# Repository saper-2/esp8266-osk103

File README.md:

# Rotenso ESP8266-OSK103

This is basically a my version of Sergey's [IoT-Uni-Dongle](https://github.com/dudanov/iot-uni-dongle) . I have created this for my Rotenso branded A/C (and any other A/C that take OSK103 or newer OSK105 wifi module). 

---
**Why**
Someone who see this first time will think **Why**. First, for me it is: **I DO NOT TRUST CHINESE CLOUD**, why I would potentially let someone into my network? Even if those modules don't have this kind of "feature" (supposedly :upside_down_face:). 

E.g.: for hackers that got into manufacturer servers would be then simple to remotely upload firmware that would create encrypted tunnel from their server to inside my home network. Well, someone can say this won't happen, but I in last year, I read about chinese server hacked and that company stayed quiet about it, until stolen data made into black market and started popping up everywhere...

And, there is another much simpler reason: when my internet connection fail then those "cloud-based" solution go to hike... You can't control them via phone being in home (and looking for remote in this case can be PITA :sweat_smile: ), but with custom module that connect to your local server (HomeAssistant, or MQTT, ...) you still in control :grin: 

---

There is not much to write about the module circuit it basically that same. I have made PCB so it can be used with USB male SMT plug, or pinheader/goldpin or JST 2.5mm 4pin (or 5pin if IR is used) or wires just soldered to it. I placed a small 6pin 1mm connector for potential programming, and also testpoint pads that are used by designed especially for this module Programming Rig (cradle).

It's 2nd revision - don't ask about 1st one :upside_down_face:

---

# Part List

## Module

See notes under the list too.

REF | QTY | VAL | Footprint | P/N
--- | --- | --- | --- | ---
C1 C4 | 2 | 100n | C_0402_HS | |
C2 C3 | 2| 22/10V| CP_3216-HS
C5 | 1| 1u| C_0402_HS
C6 | 1| 470p| C_0805_HS
C7 | 1| 15/6,3V| CP_3216-HS
D1 | 1| G| LED0603_HS
D2 | 1| Or| LED0603_HS
D3 | 1| Y| LED0603_HS
FB1 | 1| Z600| R_0805_HS|
J1 | 1| *notes*| 
J2 | 1| *notes*| 
J3*| 1| *notes*| 
M1 | 1| ESP-12E| ESP-12E
R1 R8 R9 | 3| 4k3| R_0402_HS
R10 R12 | 2| 10k| R_0402_HS
R13* R14* | 2| 10k| R_0402_HS2
R15* | 1| 470R| R_0603_HS
R2 R3 | 2| 22R| R_0402_HS
R4 R5 R6 R7 R11 | 5| 22k| R_0402_HS
SW1, SW2| 2| BOOT, RST| KXT321LHS| (C&K) KXT321LHS
T1 T2* | 2| RK7002DW| SC-70-6_HS
U1 | 1| 1117-33| SOT-223-3

***Notes:***
**Install either J1 or J2 only.**

J1: it can be goldpin 4 or 5pin (if you want IR too) or JST 2.5mm socket (4/5pin), or just solder wires directly to pads.

J2: It is USB male SMD plug that fit footprint of Molex ```48037-2200``` - so basically most of USB SMD plugs should fit, but if you have key in socket in your AC read further for fixing the usb plug to fit keyed socket.

J3 - optional, this is for programming/debugging - I have used 6pin 1mm pitch SMT right angled socket (JST code: ```SM06B-SRSS-TB(LF)(SN)``` but any similar will do: ```JS-1254R-06``` or ```WE06DH``` )

**No IR Version**
You can skip ```R13..R15 & T2``` - those are only for IR support (tapping into IR receiver).

**IR version**
You can tap into IR receiver on display board - then R15 is not needed.

Or you can add a small IR diode if you don't want to mess with your display board:
``` [pad_IR+]---[A]-|>|-[C]---[IR_pad] ```

*A - IR diode anode , C - IR diode cathode*

## Rig / Cradle

Not much of list :smile: :
* Ppring test probe socket: ```R50-2C``` - 7pcs ,
* Sprint test probe: ```P50-E2```- 7pcs ,
* Goldpin 1x7 - 1pcs ,
* Goldpin 1x2 - 1pcs ,
* Goldpin 1x3 - 1pcs ,
* Jumper bridge - 1pcs .

---

# Assembly

## ESP8266-OSK103
If you not need to tap into IR then you can just skip: ```R13, R14, R15, T2``` . BOOT button is optional too.

### Hacking USB plug

For USB connector you have to check your AC, if you have special "keys" in usb socket:

Then you have to disassembly USB plug before soldering and cut-up a bit of the plastic:

It should have not more than 9.00-9.1mm width after cut.

To remove the insert grab the plug and push-out the insert with flat screwdriver:
 
Holding it like that make it much easier to push out.

Then use sharp knife, file or even mill if you have (then you don't need to mill down all the plastic, you can leave about 1..2mm from bottom :smile: ) to remove sides of the insert front part (with contacts).

## Programming Rig

I have used spring test probes (you can find it also under name: spring pogo pins):

Everything was printed on Ender 3 (v1) layer 0.12mm/nozzle 0.4mm .
Only the: arm, top part and bottom spring retainer had a higher infill (about 50-60%). Top part was printed with at least 3 walls (or 4 - don't remember exactly :sweat_smile: )
Arm was printed on side with "everywhere support" enabled .

STLs you can grab from Thingiverse: [ESP8266-OSK103 Programing Cradle](https://www.thingiverse.com/thing:5463984)

For soldering spring probes sockets to the rib pcb, I used 2nd rig pcb, and placed it on some spacers (~10mm) from 1st, then screwed down this to base, and then inserted the sockets. And making sure that they are straight, with hot solder iron that have on tip a melted tin , I quickly soldered socket to 1st board pad - be quick to not melt the base plastic where spring probe socket sits in guide in base part.

After that, just remove 2nd board and you can end soldering cradle board and push in spring probes.

For assembling I used few screws for metal: 3x6, 3x10 , and few M3: M3x10 , M3x12 and M3x20 + 2 M3 nuts (just what I have lying around).

# Other notes

In ```3d``` you'll find the design files for cradle - it was done in Design Spark Mechanical.

In ```pcb`` you''' find all PCB design files, PDFs with schematics and BOMs, also gerber files for pcb fab too.

I am sorry all English speaking people for messing up with ```cradle``` word - I often swap the letters :sweat_smile: sorry :pleading_face: 

In ```photos``` there is few more photos how this looks like.

# EOF

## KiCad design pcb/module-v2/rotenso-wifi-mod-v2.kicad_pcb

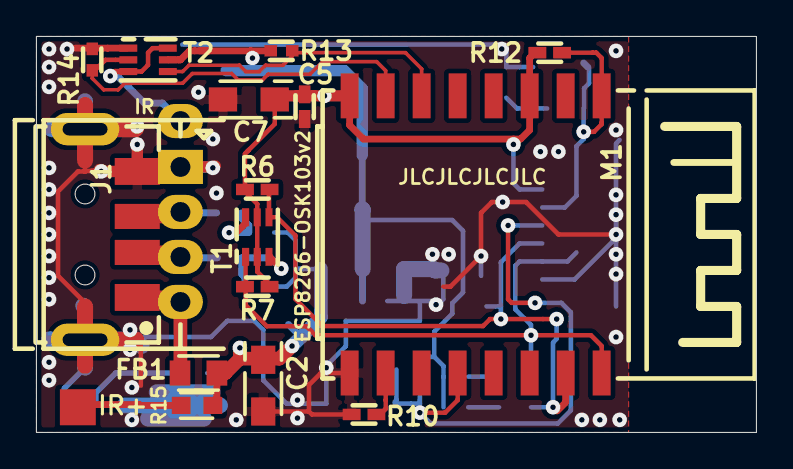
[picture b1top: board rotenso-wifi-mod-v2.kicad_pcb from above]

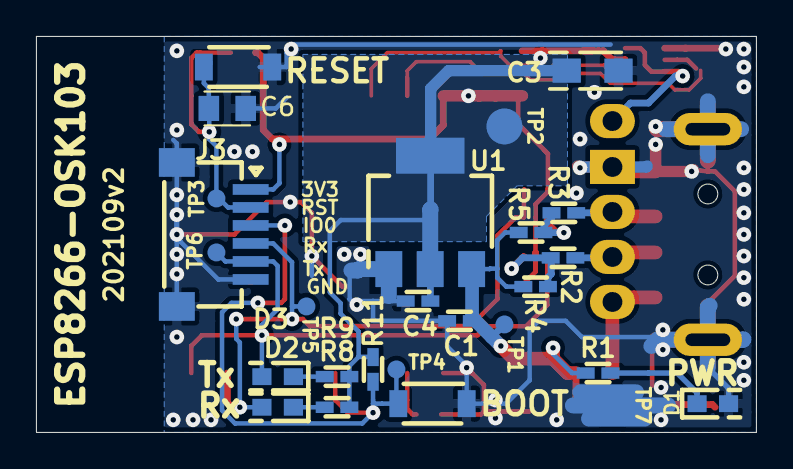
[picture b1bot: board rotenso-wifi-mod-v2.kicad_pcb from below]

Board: 2 copper layers, 40.0 x 22.0 mm, 44 parts (26 on the bottom side), 20 nets.

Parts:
C1, C4: 100n; C_0402_HS
C2, C3: 22/10V; CP_3216-HS
C5: 1u; C_0402_HS
C6: 470p; C_0805_HS
C7: 15/6,3V; CP_3216-HS
D1: G; LED0603_HS
D2: Or; LED0603_HS
D3: Y; LED0603_HS
FB1: Z600; R_0805_HS
J1: JST-XH(4p 2.5mm); WG04R-2.5-04P-H
J2: USBPlug; USB_Plug_Molex_48037-2200
J3: ESP_FLASH_CONN; WE06DH-1.0-06P-H
M1: ESP8266_ESP-12E; ESP-12E
P1: IR; WG00x-2.5-00-V-PAD
P2: IR+; SMT_PAD_2x2mm_noFrame
R1, R8, R9: 4k3; R_0402_HS
R2, R3: 22R; R_0402_HS
R4, R5, R6, R7, R11: 22k; R_0402_HS
R10, R12: 10k; R_0402_HS
R13, R14: 10k; R_0402_HS2
R15: 470R; R_0603_HS
SW1: BOOT; CK_KXT3
SW2: RESET; CK_KXT3
T1, T2: RK7002DW; SOT-363_SC-70-6_HS
TP1, TP3, TP4, TP5, TP6: TP; SMT_PAD_1mm_noFrame
TP2, TP7: TP; SMT_PAD_2mm_noFrame
U1: 1117-33; SOT-223-3

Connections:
+5V: C1.1, C2.1, FB1.1, R1.1, R4.1, R5.1, R15.1, TP1.1, U1.3
/IO0: J3.3, M1.12, R11.2, SW1.1, TP4.1
/IO12R: M1.6, R13.2, T2.4
/IO13T: M1.7, R14.1, T2.2
/IO15: M1.10, R10.1
/RST: C6.1, J3.2, M1.1, R12.2, SW2.1, TP3.1
/Rx: D2.1, J3.4, M1.15, R6.2, T1.4, TP5.1
/RxAC: R3.2, R5.2, T1.6
/Tx: D3.1, J3.5, M1.16, R7.2, T1.1, TP6.1
/TxAC: R2.2, R4.2, T1.3
GND: C1.2, C2.2, C3.2, C4.2, C5.2, C6.2, C7.2, D1.1, J1.1, J2.4, J2.5, J3.6, J3.X1, J3.X2, M1.9, R10.2, R14.2, SW1.2, SW2.2, T2.1, TP7.1, U1.1
unnamed: D1.2, R1.2
unnamed: D2.2, R8.2
unnamed: D3.2, R9.2
unnamed: FB1.2, J1.4, J2.1
unnamed: J1.2, J2.3, R3.1
unnamed: J1.3, J2.2, R2.1
unnamed: P1.1, T2.3, T2.6
unnamed: P2.1, R15.2
VCC: C3.1, C4.1, C5.1, C7.1, J3.1, M1.3, M1.8, R6.1, R7.1, R8.1, R9.1, R11.1, R12.1, R13.1, T1.2, T1.5, T2.5, TP2.1, U1.2

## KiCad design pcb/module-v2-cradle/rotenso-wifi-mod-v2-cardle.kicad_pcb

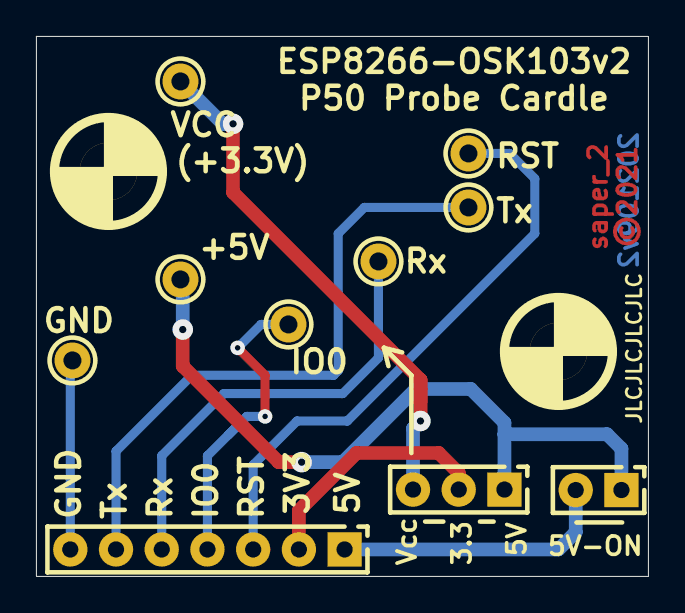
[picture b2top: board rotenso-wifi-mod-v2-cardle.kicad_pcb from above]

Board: 2 copper layers, 34.0 x 30.0 mm, 12 parts (0 on the bottom side), 9 nets.

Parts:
J1: PROG; HDR1X07_V
JP1: PowerSel; HDR1X03_V
JP2: 5V-ON; HDR1X02_V
MH1, MH3: 3mm; MHOLE-3.2MM
TP1, TP2, TP3, TP4, TP5, TP6, TP7: TP; PAD_SpingProbe_R50-2C

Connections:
+5V: JP1.1, JP2.1, TP1.1
/3V3: J1.2, JP1.2
/5V: J1.1, JP2.2
/IO0: J1.4, TP4.1
/RST: J1.3, TP3.1
/Rx: J1.5, TP5.1
/Tx: J1.6, TP6.1
GND: J1.7, TP7.1
VCC: JP1.3, TP2.1

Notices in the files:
pcb/module-v2-cradle/rotenso-wifi-mod-v2-cardle.kicad_pcb:
©2021
